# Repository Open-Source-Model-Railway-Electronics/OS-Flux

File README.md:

# OS-Flux

The OS-Flux is a tiny open-source DCC decoder built around an ATtiny85 with four LED/function outputs. It fits inside a signal housing or a locomotive.
Flashed with the Flux-Signal firmware it is a signal decoder that drives up to 4 signal lamps, steady or blinking, via DCC extended accessory commands or turnout commands.
Flashed with the Flux-Mobile firmware it is a locomotive function decoder with directional headlights and CV-configurable auxiliary outputs.

📖 [Manual](docs/Manual-EN.md)

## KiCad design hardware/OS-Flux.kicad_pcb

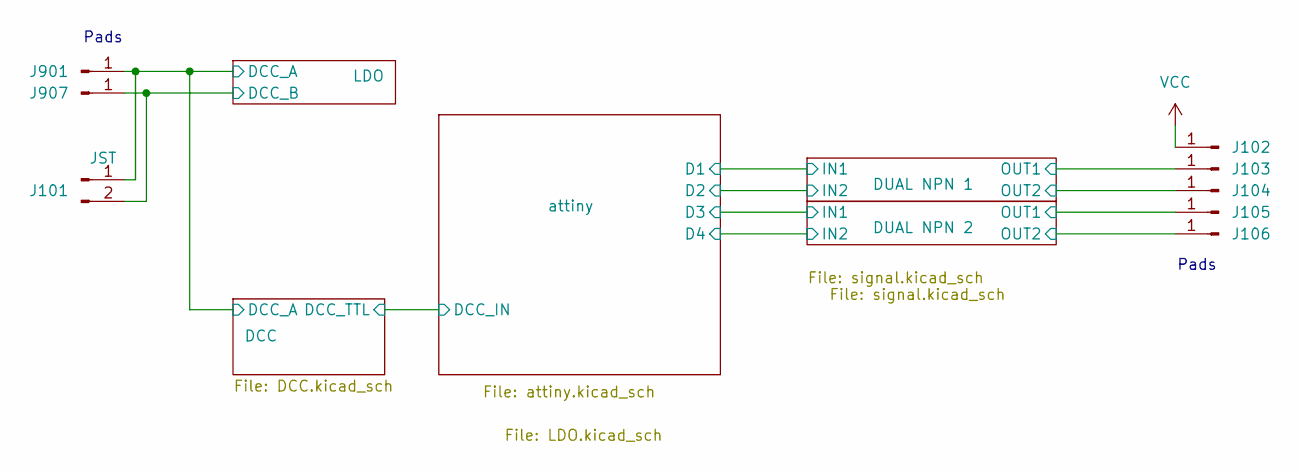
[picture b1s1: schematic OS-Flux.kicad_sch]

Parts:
J101: JST; JST_SH_SM02B-SRSS-TB_1x02-1MP_P1.00mm_Horizontal
J102, J103, J104, J105, J106, J901, J907: Conn_01x01_Pin; SolderWirePad_1x01_SMD_1x2mm

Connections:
/DCC/DCC_A: J101.1, J901.1; also elsewhere on the board
/DUAL NPN 1/OUT1: J103.1; also elsewhere on the board
/DUAL NPN 1/OUT2: J104.1; also elsewhere on the board
/DUAL NPN 2/OUT1: J105.1; also elsewhere on the board
/DUAL NPN 2/OUT2: J106.1; also elsewhere on the board
/LDO/DCC_B: J101.2, J907.1; also elsewhere on the board
VCC: J102.1; also elsewhere on the board

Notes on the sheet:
Pads

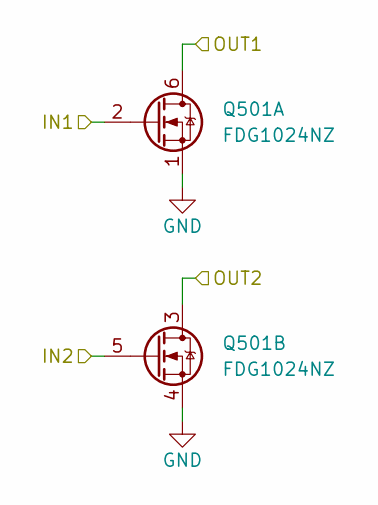
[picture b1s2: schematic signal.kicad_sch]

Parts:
Q501: FDG1024NZ; SOT-363_SC-70-6; JLCPCB Part# C262138

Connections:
/DUAL NPN 1/IN1: Q501.2 (G); also elsewhere on the board
/DUAL NPN 1/IN2: Q501.5 (G); also elsewhere on the board
/DUAL NPN 1/OUT1: Q501.6 (D); also elsewhere on the board
/DUAL NPN 1/OUT2: Q501.3 (D); also elsewhere on the board
GND: Q501.1 (S), Q501.4 (S); also elsewhere on the board

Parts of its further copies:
Q502: FDG1024NZ; SOT-363_SC-70-6; JLCPCB Part# C262138

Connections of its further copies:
/DUAL NPN 2/OUT1: Q502.6 (D); also elsewhere on the board
/DUAL NPN 2/OUT2: Q502.3 (D); also elsewhere on the board
/attiny/MISO: Q502.2 (G); also elsewhere on the board
/attiny/MOSI: Q502.5 (G); also elsewhere on the board
GND: Q502.1 (S), Q502.4 (S); also elsewhere on the board

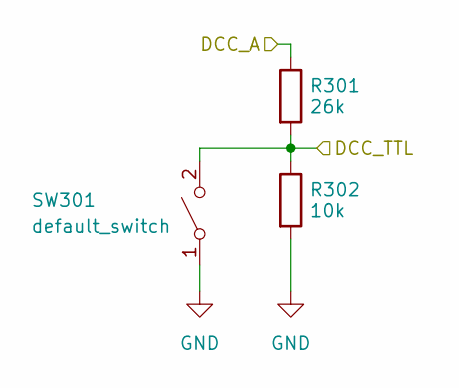
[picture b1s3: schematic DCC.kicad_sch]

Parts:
R301: 26k; R_0402_1005Metric; JLCPCB Part# C25771
R302: 10k; R_0402_1005Metric; JLCPCB Part# C25744
SW301: default_switch; JLCPCB Part# C318884

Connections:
/attiny/SCK: SW301.2 (B); also elsewhere on the board
GND: SW301.1 (A); also elsewhere on the board

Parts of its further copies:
R2: 26k; R_0402_1005Metric; JLCPCB Part# C25771
R3: 10k; R_0402_1005Metric; JLCPCB Part# C25744

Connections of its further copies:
/DCC/DCC_A: R2.1; also elsewhere on the board
/attiny/SCK: R2.2, R3.1; also elsewhere on the board
GND: R3.2; also elsewhere on the board

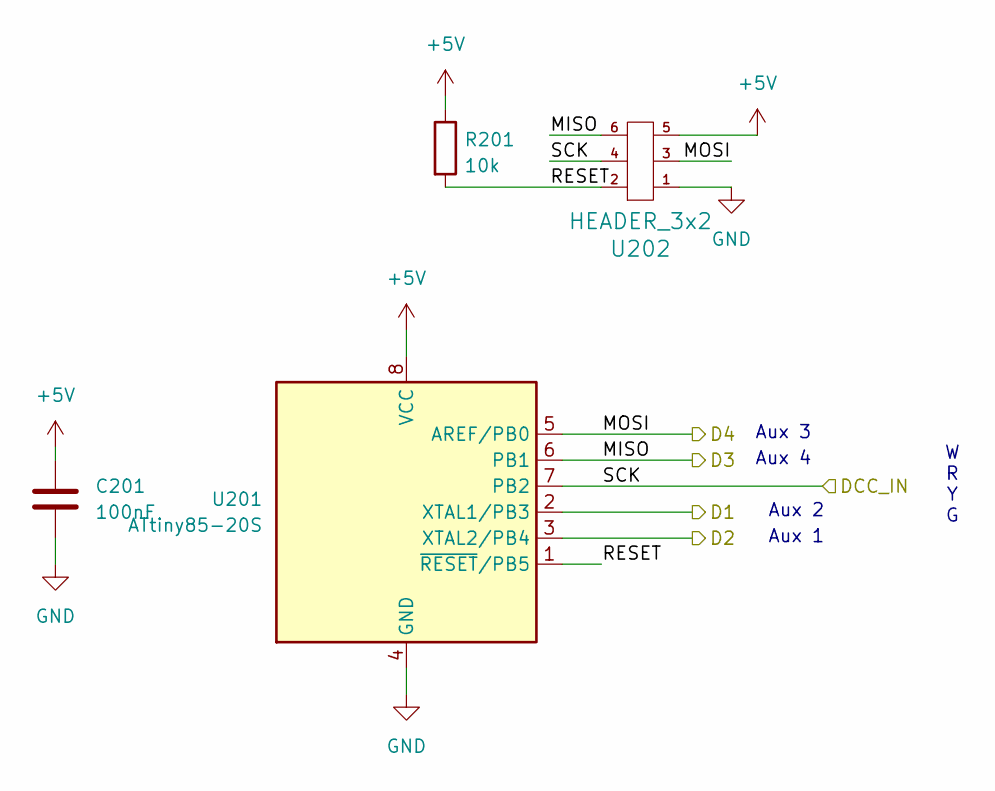
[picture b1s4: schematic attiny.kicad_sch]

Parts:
C201: 100nF; C_0402_1005Metric; JLCPCB Part# C307331
R201: 10k; R_0402_1005Metric; JLCPCB Part# C25744
U201: ATtiny85-20S; SOIC-8W_5.3x5.3mm_P1.27mm; JLCPCB Part# C615549
U202: HEADER_3x2; PinSocket_2x03_P1.27mm_Vertical

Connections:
+5V: C201.1, R201.1, U201.8 (VCC), U202.5; also elsewhere on the board
/DUAL NPN 1/IN1: U201.2 (XTAL1/PB3); also elsewhere on the board
/DUAL NPN 1/IN2: U201.3 (XTAL2/PB4); also elsewhere on the board
/attiny/MISO: U201.6 (PB1), U202.6; also elsewhere on the board
/attiny/MOSI: U201.5 (AREF/PB0), U202.3; also elsewhere on the board
/attiny/RESET: R201.2, U201.1 (~RESET/PB5), U202.2
/attiny/SCK: U201.7 (PB2), U202.4; also elsewhere on the board
GND: C201.2, U201.4 (GND), U202.1; also elsewhere on the board

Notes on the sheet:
W R Y G
Aux 2
Aux 1
Aux 3
Aux 4

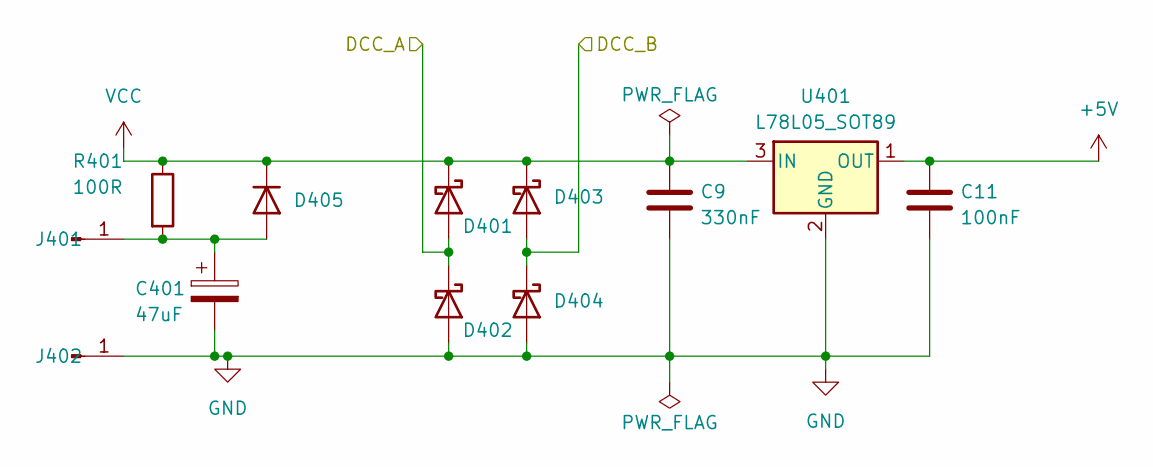
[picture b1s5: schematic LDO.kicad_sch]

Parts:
C9: 330nF; C_0603_1608Metric; JLCPCB Part# C1615
C11: 100nF; C_0402_1005Metric; JLCPCB Part# C307331
C401: 47uF; CP_EIA-7343-31_Kemet-D; JLCPCB Part# C7228
D401, D402, D403, D404: 1N5819WS; D_SOD-323; JLCPCB Part# C191023
D405: 1N4148WS; D_SOD-323; JLCPCB Part# C2128
J401, J402: Conn_01x01_Pin; SolderWirePad_1x01_SMD_1x2mm
R401: 100R; R_0402_NO_SILK; JLCPCB Part# C25076
U401: L78L05_SOT89; SOT-89-3; JLCPCB Part# C71136

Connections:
+5V: C11.1, U401.1 (OUT); also elsewhere on the board
/DCC/DCC_A: D401.2 (A), D402.1 (K); also elsewhere on the board
/LDO/DCC_B: D403.2 (A), D404.1 (K); also elsewhere on the board
GND: C9.2, C11.2, C401.2, D402.2 (A), D404.2 (A), J402.1, U401.2 (GND); also elsewhere on the board
unnamed: C401.1, D405.2 (A), J401.1, R401.2
VCC: C9.1, D401.1 (K), D403.1 (K), D405.1 (K), R401.1, U401.3 (IN); also elsewhere on the board

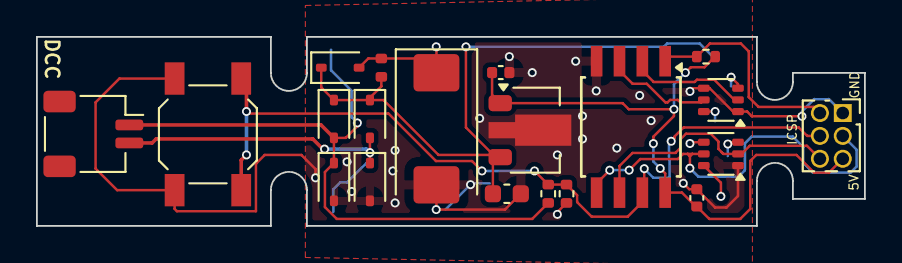
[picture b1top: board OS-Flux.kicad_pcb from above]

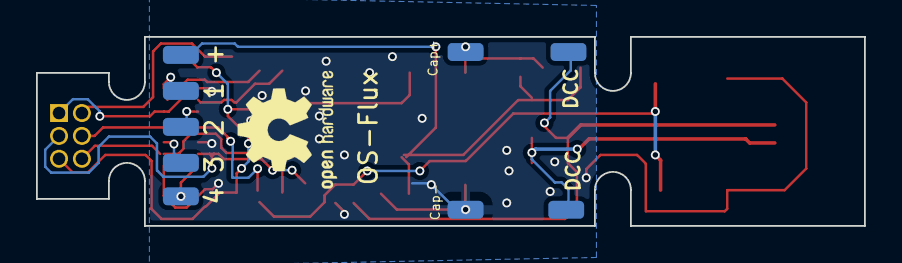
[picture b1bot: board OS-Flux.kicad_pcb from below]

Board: 2 copper layers, 46.0 x 10.5 mm, 29 parts (9 on the bottom side), 16 nets.
